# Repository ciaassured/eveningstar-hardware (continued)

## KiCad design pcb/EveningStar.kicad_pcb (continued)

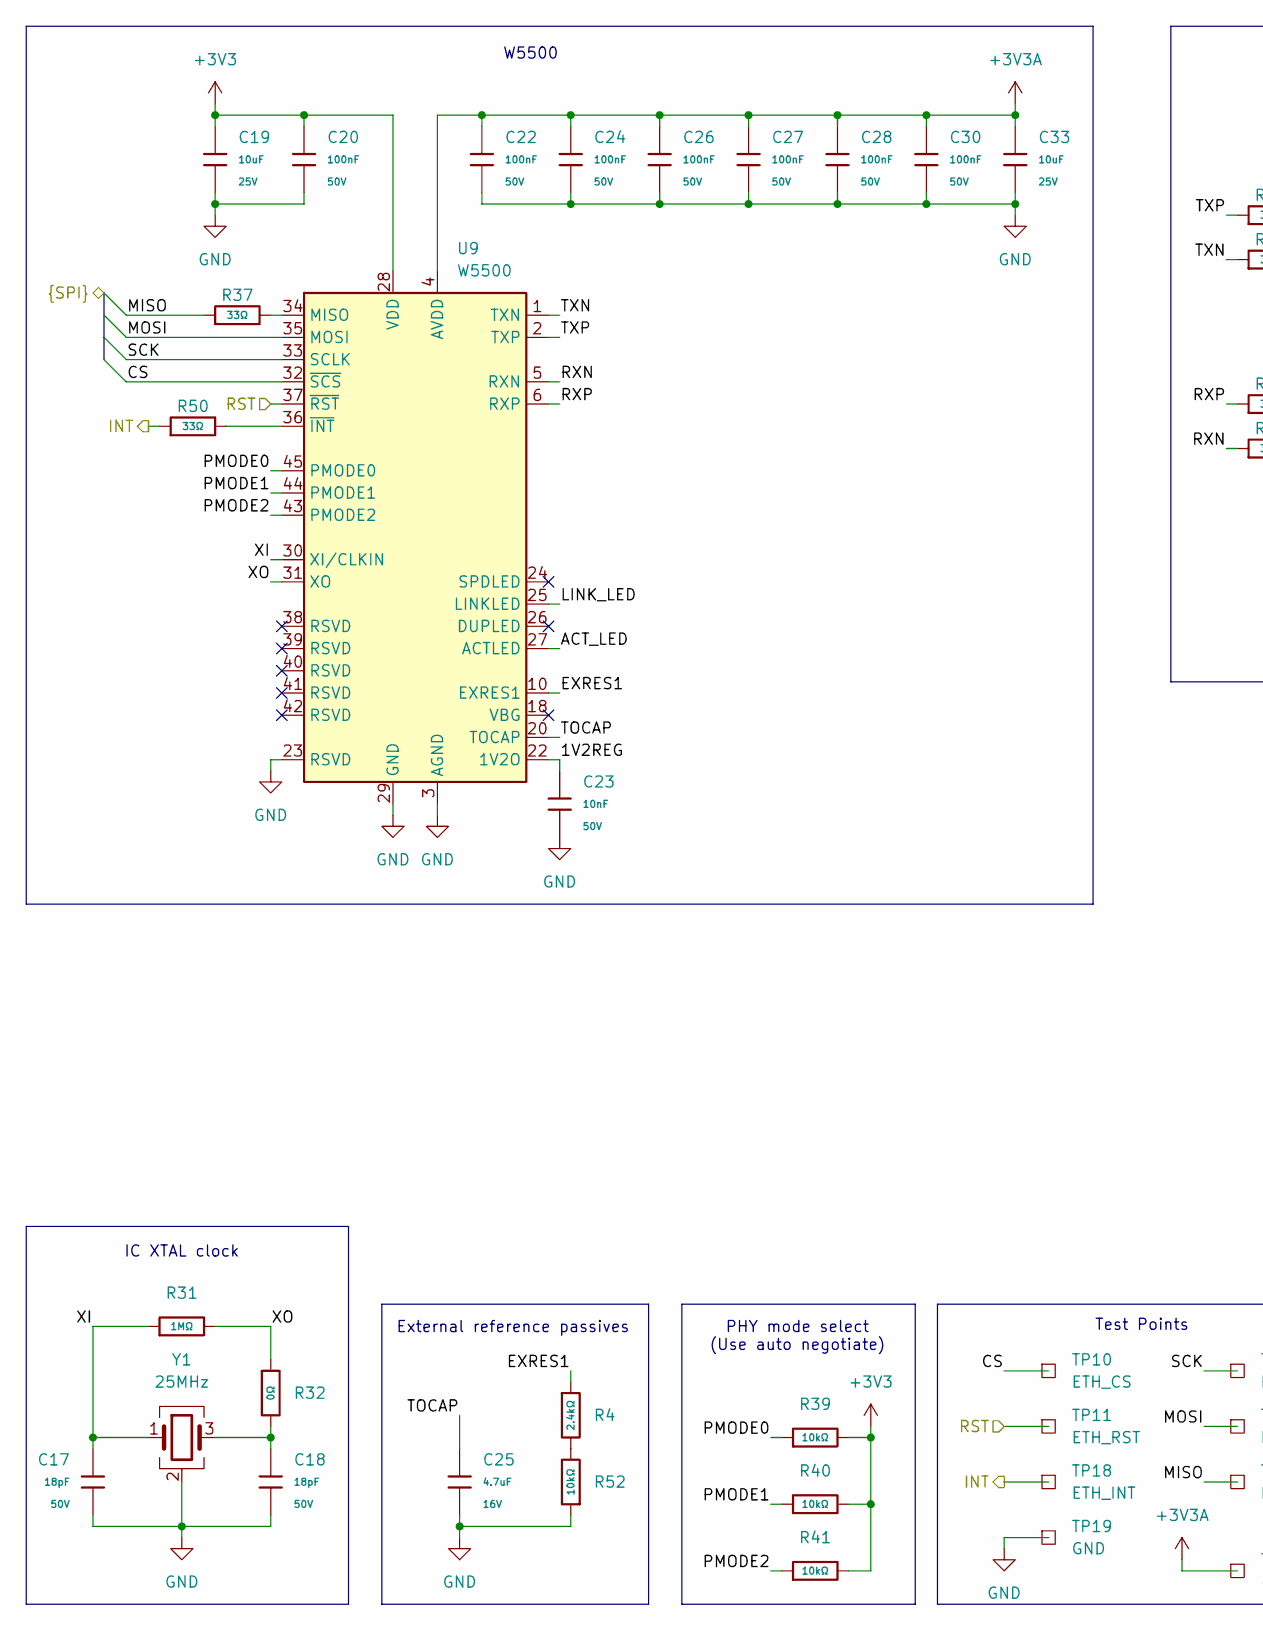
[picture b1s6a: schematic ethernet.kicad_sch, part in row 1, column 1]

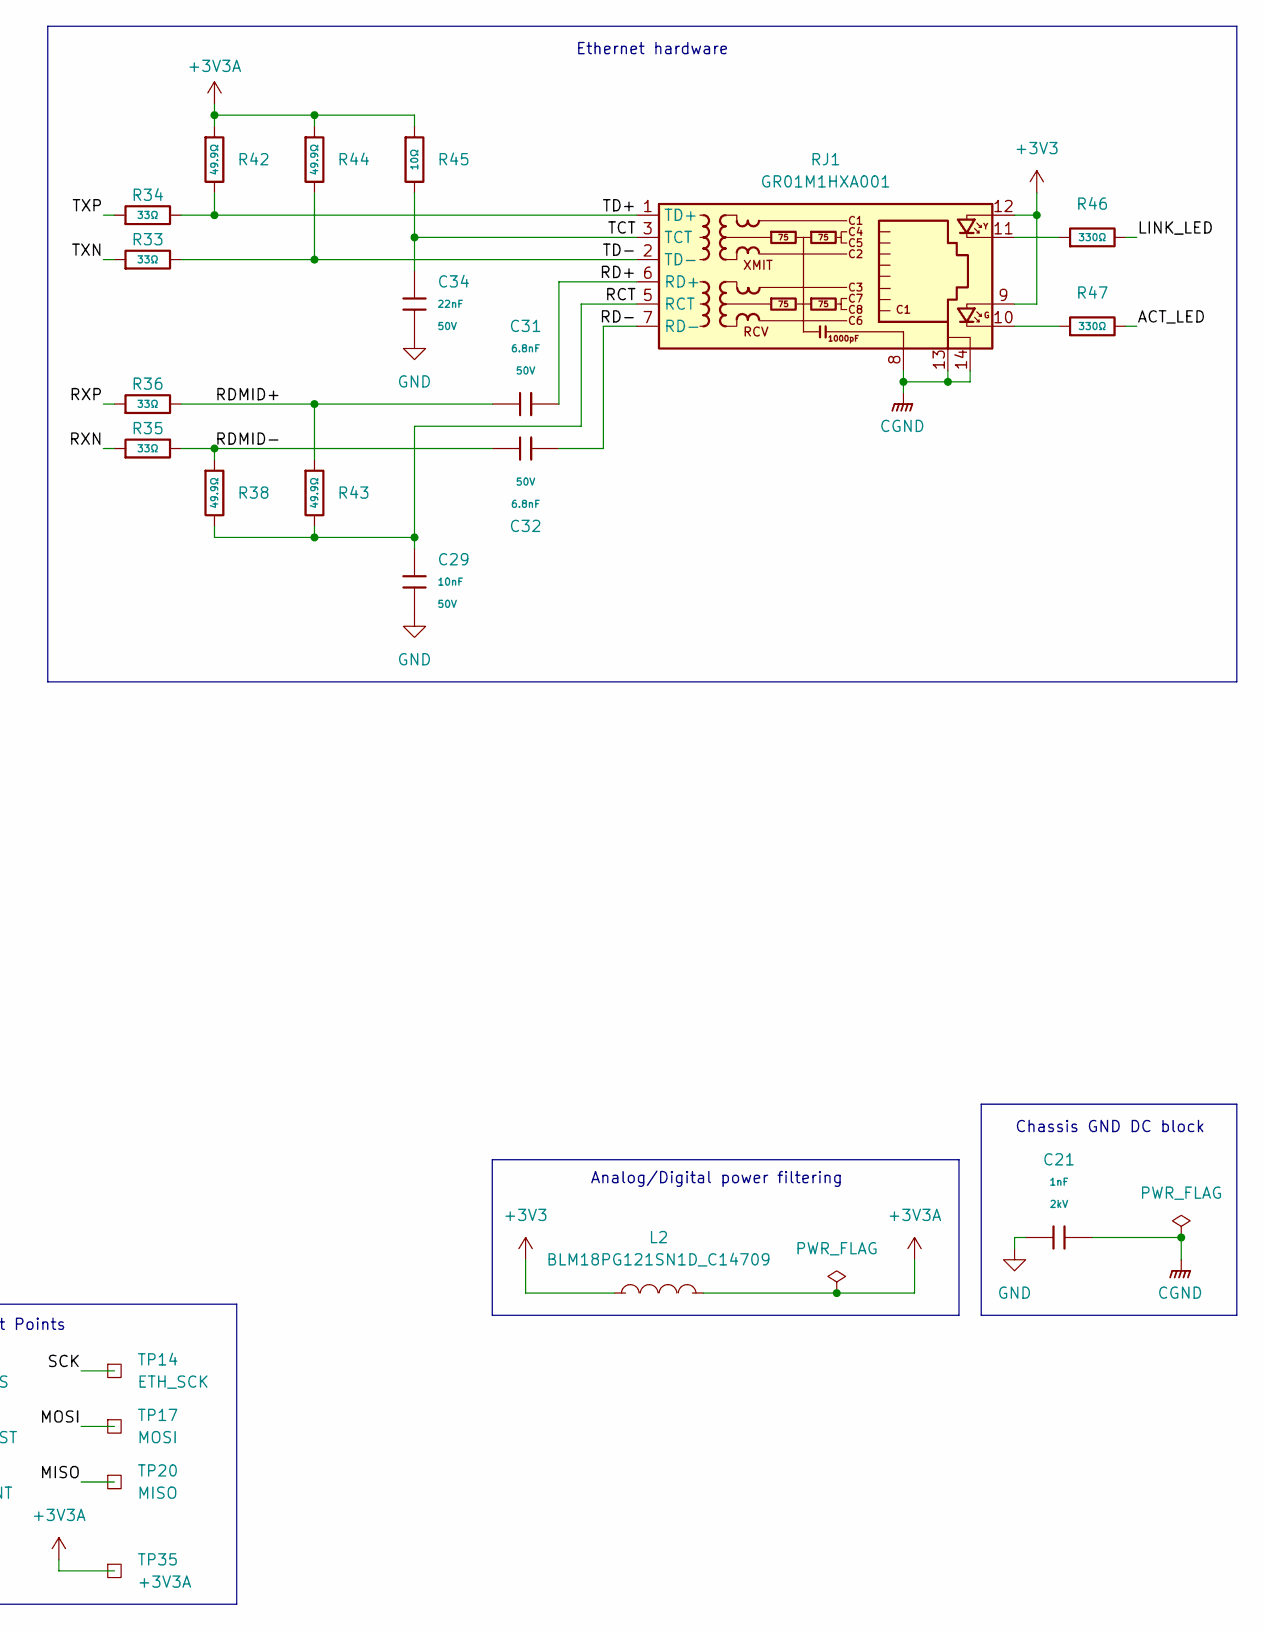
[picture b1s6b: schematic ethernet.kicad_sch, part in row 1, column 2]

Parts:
C17, C18: 18pF; C_0603; Voltage Rated 50V; Tolerance ±5%; Part CL10C180JB8NNNC; LCSC C1647
C19, C33: 10uF; C_0603; Voltage Rated 25V; Tolerance ±20%; Part CL10A106MA8NRNC; LCSC C96446
C20, C22, C24, C26, C27, C28, C30: 100nF; C_0603; Voltage Rated 50V; Tolerance ±10%; Part CC0603KRX7R9BB104; LCSC C14663
C21: 1nF; C_1206; Voltage Rated 2kV; Tolerance ±10%; Part 1206B102K202NT; LCSC C9196
C23, C29: 10nF; C_0603; Voltage Rated 50V; Tolerance ±10%; Part 0603B103K500NT; LCSC C57112
C25: 4.7uF; C_0603; Voltage Rated 16V; Tolerance ±10%; Part CL10A475KO8NNNC; LCSC C19666
C31, C32: 6.8nF; C_0603; Voltage Rated 50V; Tolerance ±10%; Part 0603B682K500NT; LCSC C1631
C34: 22nF; C_0603; Voltage Rated 50V; Tolerance ±10%; Part CL10B223KB8NNNC; LCSC C21122
L2: BLM18PG121SN1D_C14709; L0603; MPN BLM18PG121SN1D; LCSC Part C14709
R4: 2.4kΩ; R_0603; Overload Voltage (Max) 75V; Tolerance ±1%; Part 0603WAF2401T5E; LCSC C22940
R31: 1MΩ; R_0603; Overload Voltage (Max) 75V; Tolerance ±1%; Part 0603WAF1004T5E; LCSC C22935
R32: 0Ω; R_0603; Overload Voltage (Max) 75V; Tolerance ±1%; Part 0603WAF0000T5E; LCSC C21189
R33, R34, R35, R36, R37, R50: 33Ω; R_0603; Overload Voltage (Max) 75V; Tolerance ±1%; Part 0603WAF330JT5E; LCSC C23140
R38, R42, R43, R44: 49.9Ω; R_0603; Overload Voltage (Max) 75V; Tolerance ±1%; Part 0603WAF499JT5E; LCSC C23185
R39, R40, R41, R52: 10kΩ; R_0603; Overload Voltage (Max) 75V; Tolerance ±1%; Part 0603WAF1002T5E; LCSC C25804
R45: 10Ω; R_0603; Overload Voltage (Max) 75V; Tolerance ±1%; Part 0603WAF100JT5E; LCSC C22859
R46, R47: 330Ω; R_0603; Overload Voltage (Max) 75V; Tolerance ±1%; Part 0603WAF3300T5E; LCSC C23138
RJ1: GR01M1HXA001; RJ45-TH_GR01M1HXA001; MPN GR01M1HXA001; LCSC Part C4155019
TP10: ETH_CS; TestPoint_Pad_D1.0mm
TP11: ETH_RST; TestPoint_Pad_D1.0mm
TP14: ETH_SCK; TestPoint_Pad_D1.0mm
TP17: MOSI; TestPoint_Pad_D1.0mm
TP18: ETH_INT; TestPoint_Pad_D1.0mm
TP19: GND; TestPoint_Plated_Hole_D2.0mm
TP20: MISO; TestPoint_Pad_D1.0mm
TP35: +3V3A; TestPoint_Pad_D1.0mm
U9: W5500; LQFP-48_7x7mm_P0.5mm; MPN W5500; LCSC Part C32843
Y1: 25MHz; OSC-SMD_4P-L3.2-W2.5-BL; MPN X322525MOB4SI; LCSC Part C9006

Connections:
+3V3: C19.1, C20.1, L2.1, R39.2, R40.2, R41.2, RJ1.9, RJ1.12, U9.28 (VDD); also elsewhere on the board
+3V3A: C22.1, C24.1, C26.1, C27.1, C28.1, C30.1, C33.1, L2.2, R42.1, R44.1, R45.1, TP35.1 (1_1), U9.4 (AVDD), U9.8 (AVDD), U9.11 (AVDD), U9.15 (AVDD), U9.17 (AVDD), U9.21 (AVDD)
/ethernet/1V2REG: C23.1, U9.22 (1V2O)
/ethernet/ACT_LED: R47.2, U9.27 (ACTLED)
/ethernet/CS: TP10.1 (1_1), U9.32 (~SCS); also elsewhere on the board
/ethernet/EXRES1: R4.1, U9.10 (EXRES1)
/ethernet/INT: R50.1, TP18.1 (1_1); also elsewhere on the board
/ethernet/LINK_LED: R46.2, U9.25 (LINKLED)
/ethernet/MISO: R37.1, TP20.1 (1_1); also elsewhere on the board
/ethernet/MOSI: TP17.1 (1_1), U9.35 (MOSI); also elsewhere on the board
/ethernet/PMODE0: R39.1, U9.45 (PMODE0)
/ethernet/PMODE1: R40.1, U9.44 (PMODE1)
/ethernet/PMODE2: R41.1, U9.43 (PMODE2)
/ethernet/RCT: C29.1, R38.2, R43.2, RJ1.5 (RCT)
/ethernet/RD+: C31.2, RJ1.6 (RD+)
/ethernet/RD-: C32.2, RJ1.7 (RD-)
/ethernet/RDMID+: C31.1, R36.2, R43.1
/ethernet/RDMID-: C32.1, R35.2, R38.1
/ethernet/RXN: R35.1, U9.5 (RXN)
/ethernet/RXP: R36.1, U9.6 (RXP)
/ethernet/SCK: TP14.1 (1_1), U9.33 (SCLK); also elsewhere on the board
/ethernet/TCT: C34.1, R45.2, RJ1.3 (TCT)
/ethernet/TD+: R34.2, R42.2, RJ1.1 (TD+)
/ethernet/TD-: R33.2, R44.2, RJ1.2 (TD-)
/ethernet/TOCAP: C25.1, U9.20 (TOCAP)
/ethernet/TXN: R33.1, U9.1 (TXN)
/ethernet/TXP: R34.1, U9.2 (TXP)
/ethernet/XI: C17.1, R31.1, U9.30 (XI/CLKIN), Y1.1
/ethernet/XO: R31.2, R32.1, U9.31 (XO)
/mcu/ETH_RST: TP11.1 (1_1), U9.37 (~RST); also elsewhere on the board
CGND: C21.2, RJ1.8, RJ1.13, RJ1.14
GND: C17.2, C18.2, C19.2, C20.2, C21.1, C22.2, C23.2, C24.2, C25.2, C26.2, C27.2, C28.2, C29.2, C30.2, C33.2, C34.2, R52.1, TP19.1 (1_1), U9.3 (AGND), U9.9 (AGND), U9.14 (AGND), U9.16 (AGND), U9.19 (AGND), U9.23 (RSVD), U9.29 (GND), U9.48 (AGND), Y1.2 (G), Y1.4 (G); also elsewhere on the board
unnamed: C18.1, R32.2, Y1.3
unnamed: R4.2, R52.2
unnamed: R46.1, RJ1.11
unnamed: R47.1, RJ1.10
unnamed: R37.2, U9.34 (MISO)
unnamed: R50.2, U9.36 (~INT)

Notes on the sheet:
Chassis GND DC block
IC XTAL clock
W5500
Ethernet hardware
Analog/Digital power filtering
Test Points
External reference passives
PHY mode select (Use auto negotiate)

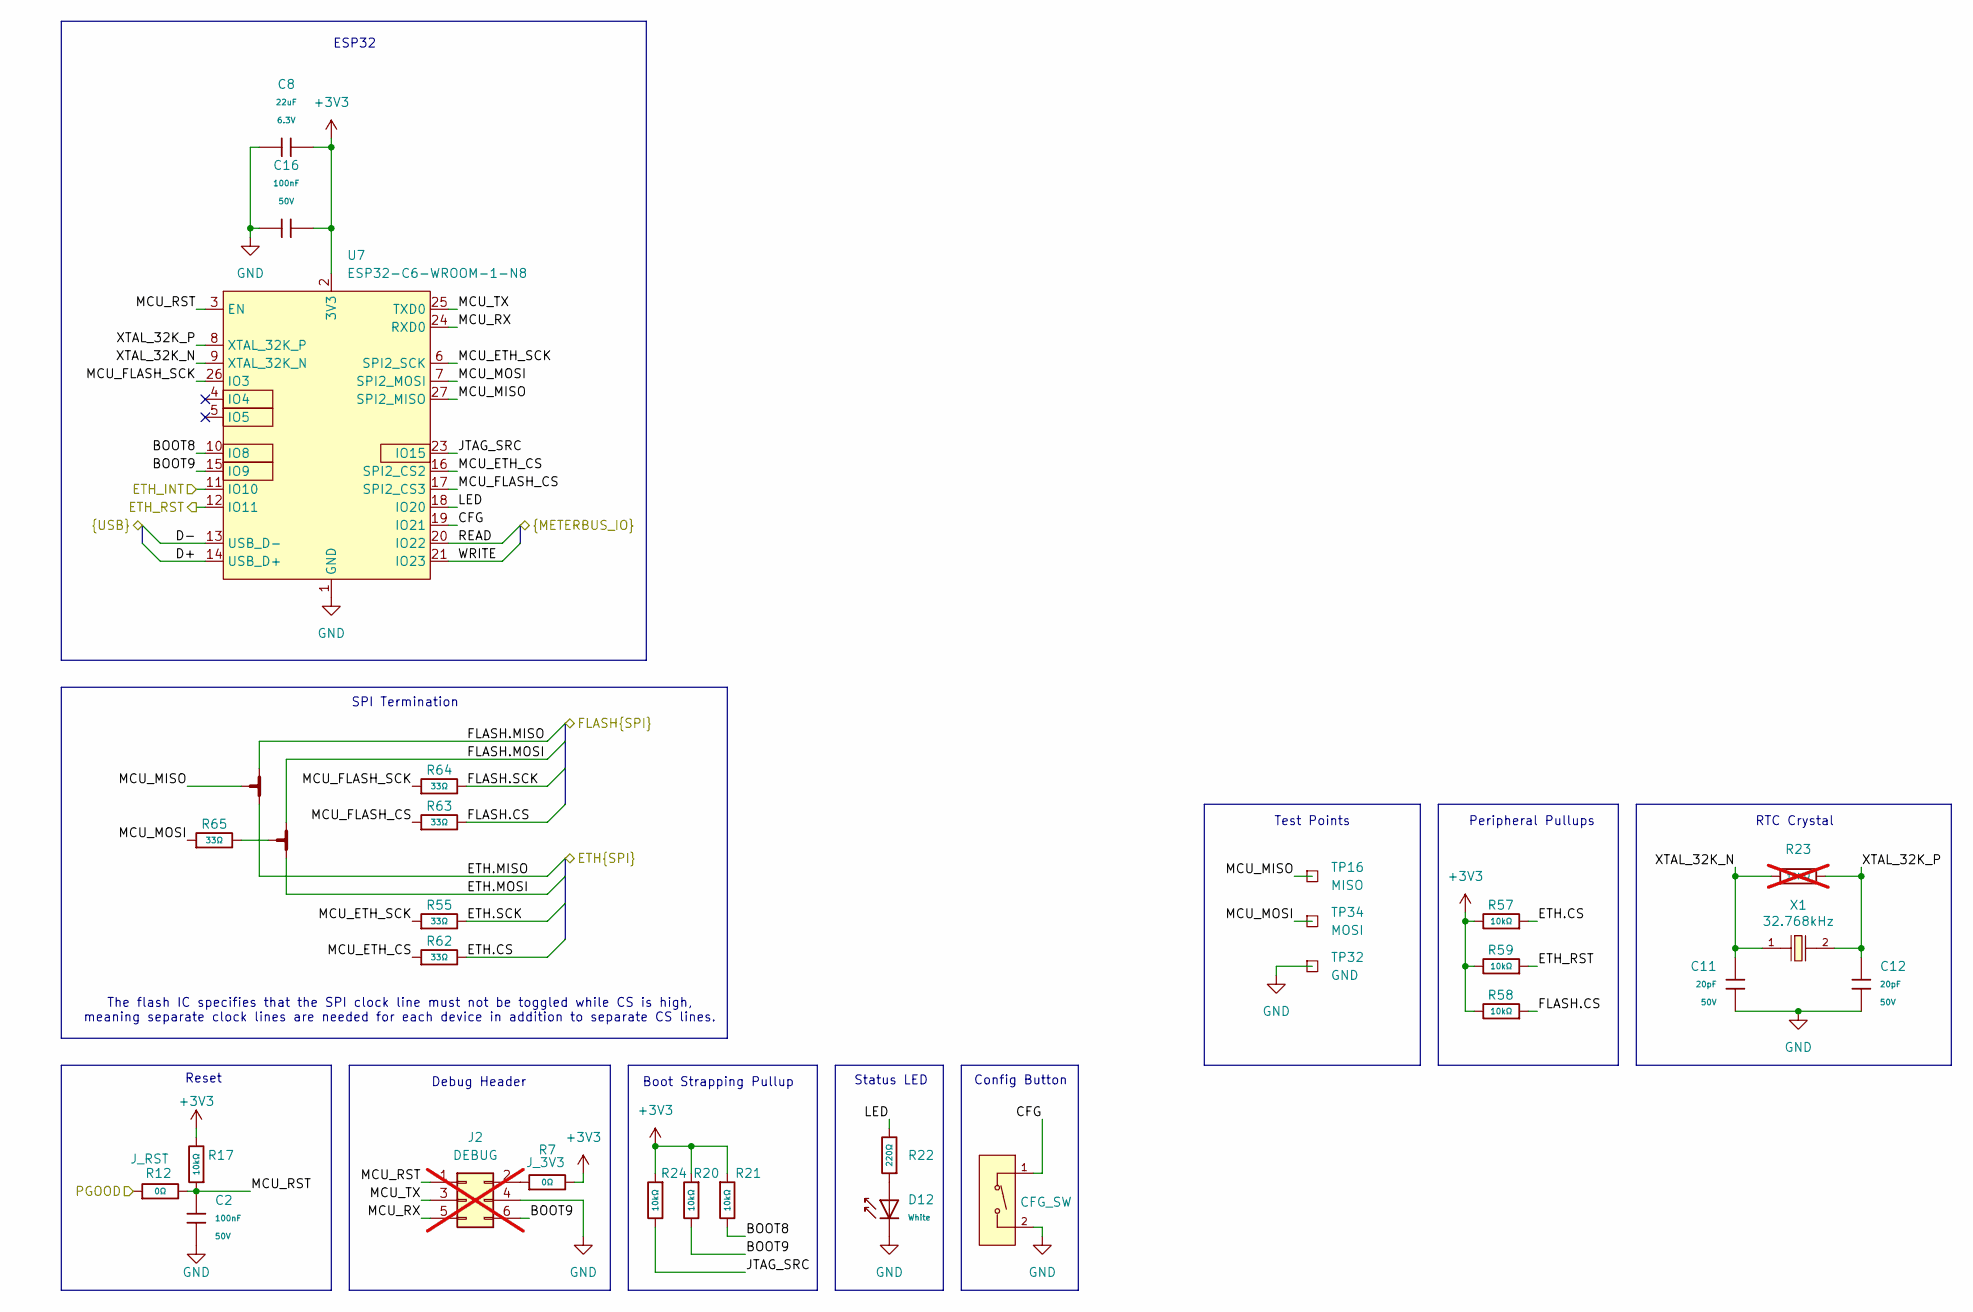
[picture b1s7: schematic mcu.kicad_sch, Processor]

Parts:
C2, C16: 100nF; C_0603; Voltage Rated 50V; Tolerance ±10%; Part CC0603KRX7R9BB104; LCSC C14663
C8: 22uF; C_0603; Voltage Rated 6.3V; Tolerance ±20%; Part CL10A226MQ8NRNC; LCSC C59461
C11, C12: 20pF; C_0603; Voltage Rated 50V; Tolerance ±5%; Part CL10C200JB8NNNC; LCSC C1648
D12: White; D_0805; Part KT-0805W; LCSC C34499
J2: DEBUG; PinHeader_2x03_P2.54mm_Vertical; not fitted
NT2: NetTie_3_Tee; NetTie-3_SMD_Pad0.5mm_Stock
NT3: NetTie_3_Tee; NetTie-3_SMD_Pad0.5mm
R7, R12: 0Ω; R_0603; Overload Voltage (Max) 75V; Tolerance ±1%; Part 0603WAF0000T5E; LCSC C21189
R17, R20, R21, R24, R57, R58, R59: 10kΩ; R_0603; Overload Voltage (Max) 75V; Tolerance ±1%; Part 0603WAF1002T5E; LCSC C25804
R22: 220Ω; R_0603; Overload Voltage (Max) 75V; Tolerance ±1%; Part 0603WAF2200T5E; LCSC C22962
R23: 10MΩ; R_0603; Overload Voltage (Max) 75V; Tolerance ±1%; Part 0603WAF1005T5E; LCSC C7250; not fitted
R55, R62, R63, R64, R65: 33Ω; R_0603; Overload Voltage (Max) 75V; Tolerance ±1%; Part 0603WAF330JT5E; LCSC C23140
S1: Tactile Button, 160gf; SW_TS-1088-AR02016; Voltage Rating (Dc) 12V; Part TS-1088-AR02016; LCSC C720477
TP16: MISO; TestPoint_Pad_D1.0mm
TP32: GND; TestPoint_Plated_Hole_D2.0mm
TP34: MOSI; TestPoint_Pad_D1.0mm
U7: ESP32-C6-WROOM-1-N8; WIRELM-SMD_ESP32-C6-WROOM-1; MPN ESP32-C6-WROOM-1-N8; LCSC Part C5366877
X1: 32.768kHz; FC-135R_L3.2-W1.5; Frequency Tolerance ±20ppm; Part Q13FC13500004; LCSC C32346

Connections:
+3V3: C8.2, C16.1, R7.2, R17.2, R20.1, R21.1, R24.1, R57.2, R58.2, R59.2, U7.2 (3V3); also elsewhere on the board
/ethernet/CS: R57.1, R62.2; also elsewhere on the board
/ethernet/INT: U7.11 (IO10); also elsewhere on the board
/ethernet/MISO: NT3.2; also elsewhere on the board
/ethernet/MOSI: NT2.2; also elsewhere on the board
/ethernet/SCK: R55.2; also elsewhere on the board
/flash/CS: R58.1, R63.2; also elsewhere on the board
/flash/MISO: NT3.1; also elsewhere on the board
/flash/MOSI: NT2.1; also elsewhere on the board
/flash/SCK: R64.2; also elsewhere on the board
/mcu/BOOT8: R21.2, U7.10 (IO8)
/mcu/BOOT9: J2.6, R20.2, U7.15 (IO9)
/mcu/CFG: S1.1 (A), U7.19 (IO21)
/mcu/D+: U7.14 (USB_D+); also elsewhere on the board
/mcu/D-: U7.13 (USB_D-); also elsewhere on the board
/mcu/ETH_RST: R59.1, U7.12 (IO11); also elsewhere on the board
/mcu/JTAG_SRC: R24.2, U7.23 (IO15)
/mcu/LED: R22.2, U7.18 (IO20)
/mcu/MCU_ETH_CS: R62.1, U7.16 (SPI2_CS2)
/mcu/MCU_ETH_SCK: R55.1, U7.6 (SPI2_SCK)
/mcu/MCU_FLASH_CS: R63.1, U7.17 (SPI2_CS3)
/mcu/MCU_FLASH_SCK: R64.1, U7.26 (IO3)
/mcu/MCU_MISO: NT3.3, TP16.1 (1_1), U7.27 (SPI2_MISO)
/mcu/MCU_MOSI: R65.1, TP34.1 (1_1), U7.7 (SPI2_MOSI)
/mcu/MCU_RST: C2.1, J2.1, R12.2, R17.1, U7.3 (EN)
/mcu/MCU_RX: J2.5, U7.24 (RXD0)
/mcu/MCU_TX: J2.3, U7.25 (TXD0)
/mcu/PGOOD: R12.1; also elsewhere on the board
/mcu/READ: U7.20 (IO22); also elsewhere on the board
/mcu/WRITE: U7.21 (IO23); also elsewhere on the board
/mcu/XTAL_32K_N: C11.1, R23.1, U7.9 (XTAL_32K_N), X1.1
/mcu/XTAL_32K_P: C12.1, R23.2, U7.8 (XTAL_32K_P), X1.2
GND: C2.2, C8.1, C11.2, C12.2, C16.2, D12.1, J2.4, S1.2 (B), TP32.1 (1_1), U7.1 (GND), U7.28 (GND), U7.29 (GND); also elsewhere on the board
unnamed: D12.2, R22.1
unnamed: J2.2, R7.1
unnamed: NT2.3, R65.2

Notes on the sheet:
Debug Header
RTC Crystal
Reset
ESP32
SPI Termination
Peripheral Pullups
The flash IC specifies that the SPI clock line must not be toggled while CS is high, meaning separate clock lines are needed for each device in addition to separate CS lines.
Status LED
Config Button
Test Points
Boot Strapping Pullup

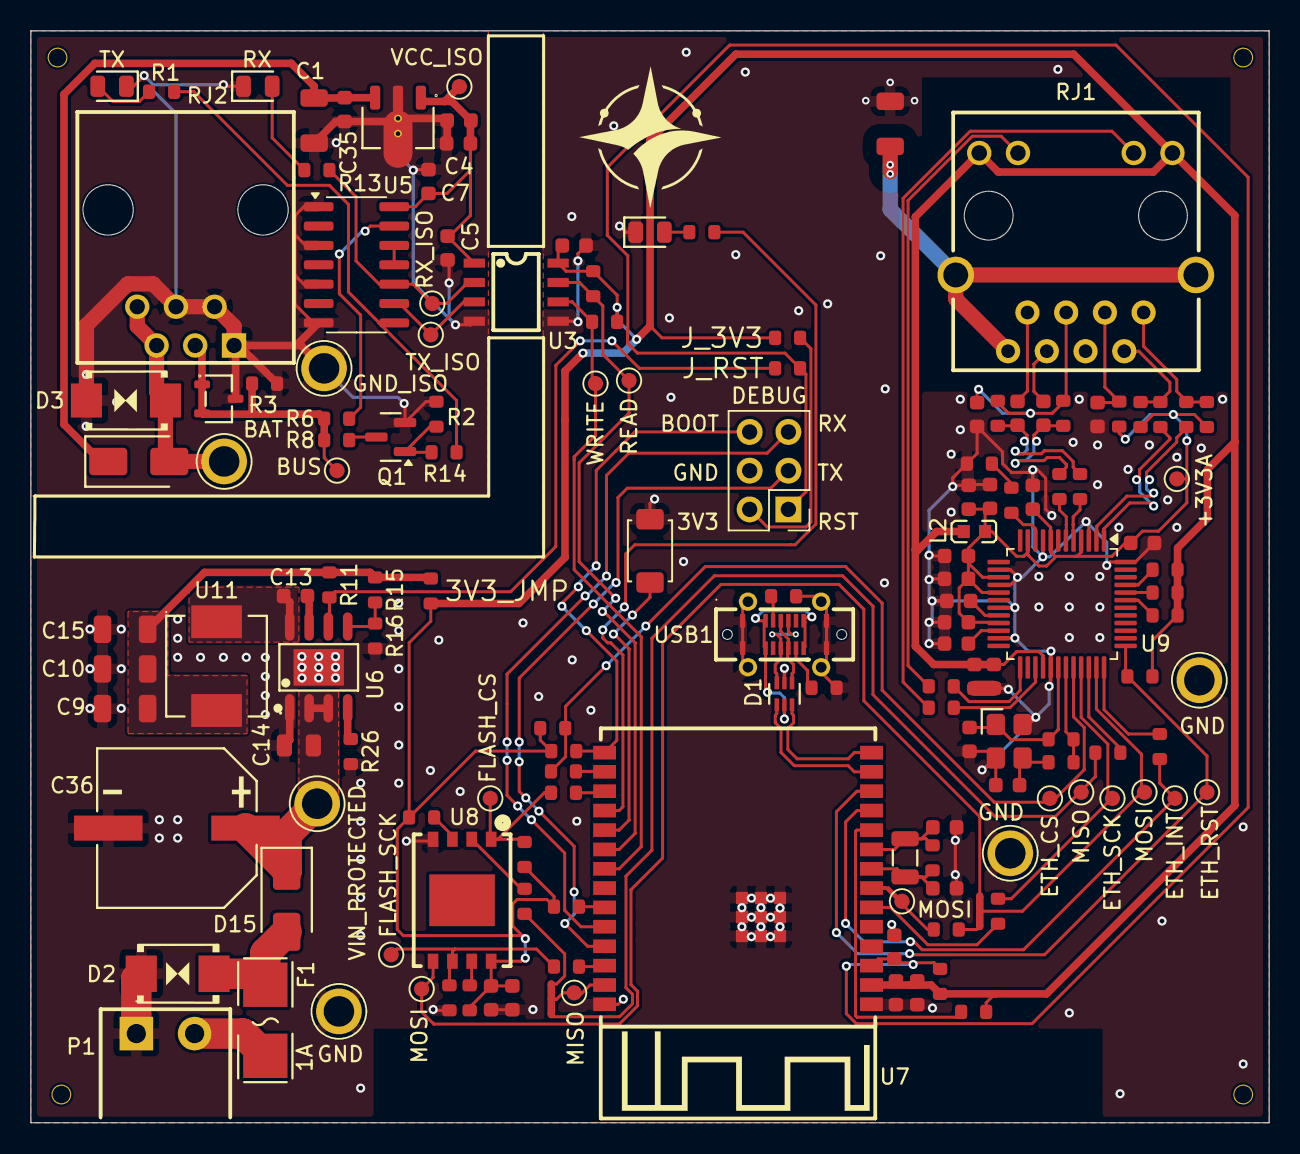
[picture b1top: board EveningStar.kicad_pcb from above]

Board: 2 copper layers, 81.2 x 71.6 mm, 152 parts (0 on the bottom side), 96 nets.

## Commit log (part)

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2026-05-12 feat: add partial design of bus interface schematic
2026-05-12 feat: add readme
2026-05-13 nfc: add documentation for meterbus voltage observations
2026-05-13 nfc: take more measurements of bus line
2026-05-13 feat: implement more of the meterbus side isolated circuit
2026-05-14 feat: add 3.3V PSU
2026-05-14 feat: add MCU sheet with USB, reset and programming circuitry
2026-05-14 feat: add W5500 ethernet controller
2026-05-14 feat: connect ethernet to mcu and sort erc errors
2026-05-15 feat: update compoents with lcsc parts
2026-05-16 feat: layout meterbus frontend
2026-05-16 fix: flip rj11 meterbus connector
2026-05-16 feat: layout ethernet
2026-05-16 feat: roughly lay out mcu
2026-05-16 feat: add filled zones
2026-05-17 feat: layout psu and rest of mcu
2026-05-17 fix: appease drc
2026-05-17 feat: create pcb production files and swap some parts for basic
2026-05-17 feat: write initial documentation for pcb ordering
2026-05-17 fix: swap meterbus tx mosfet for jlc basic part
2026-05-18 feat: replace many parts for basic parts
2026-05-18 fix: rotate parts for correct soldering
2026-05-18 feat: finish docs for ordering from jlc
2026-05-18 nfc: typo and no board change
2026-05-19 fix: add easyeda library to source control
2026-05-19 fix: add direction marker on silkscreen for AHT20
2026-05-19 fix: add missing top copper pour on meterbus side
2026-05-19 fix: update isolation keep out zone
2026-05-19 fix: add fill keep out zone for temp sensor
2026-06-21 Add ESP32 W5500 Modbus metrics sketch
2026-06-28 Squashed 'pcb/lib/JLCPCB-Kicad-Library/' content from commit bb27d66
    git-subtree-dir: pcb/lib/JLCPCB-Kicad-Library
    git-subtree-split: bb27d660dea73056d1024c0ccda3216ddcb60590
2026-06-28 pcb: add drc check action for kicad
2026-06-28 pcb: use nix for drc check script
2026-06-28 pcb: add vendored library paths
2026-06-28 pcb: remove unused symbol library
2026-06-28 pcb: update symbols and footprints to fix drc
2026-06-28 pcb: fix symbol paths for github actions check
2026-06-28 pcb: update drifted oscillator footprint
2026-06-28 pcb: add check for jlcpcb subtree lib drift
2026-06-28 pcb: switch 3d model path
2026-06-28 pcb: fix 3d offsets for parts
2026-06-28 pcb: add external reference ci check and refactor ci scripts
2026-06-28 pcb: remove 3d render action step
2026-06-28 pcb: fix easyeda 3d model path
2026-06-28 pcb: refactor custom libraries into folder
2026-06-28 pcb: add pcb readme and render script
2026-06-28 pcb: stop generating 3d models in CI/CD job
2026-06-28 pcb: add links to plugins
